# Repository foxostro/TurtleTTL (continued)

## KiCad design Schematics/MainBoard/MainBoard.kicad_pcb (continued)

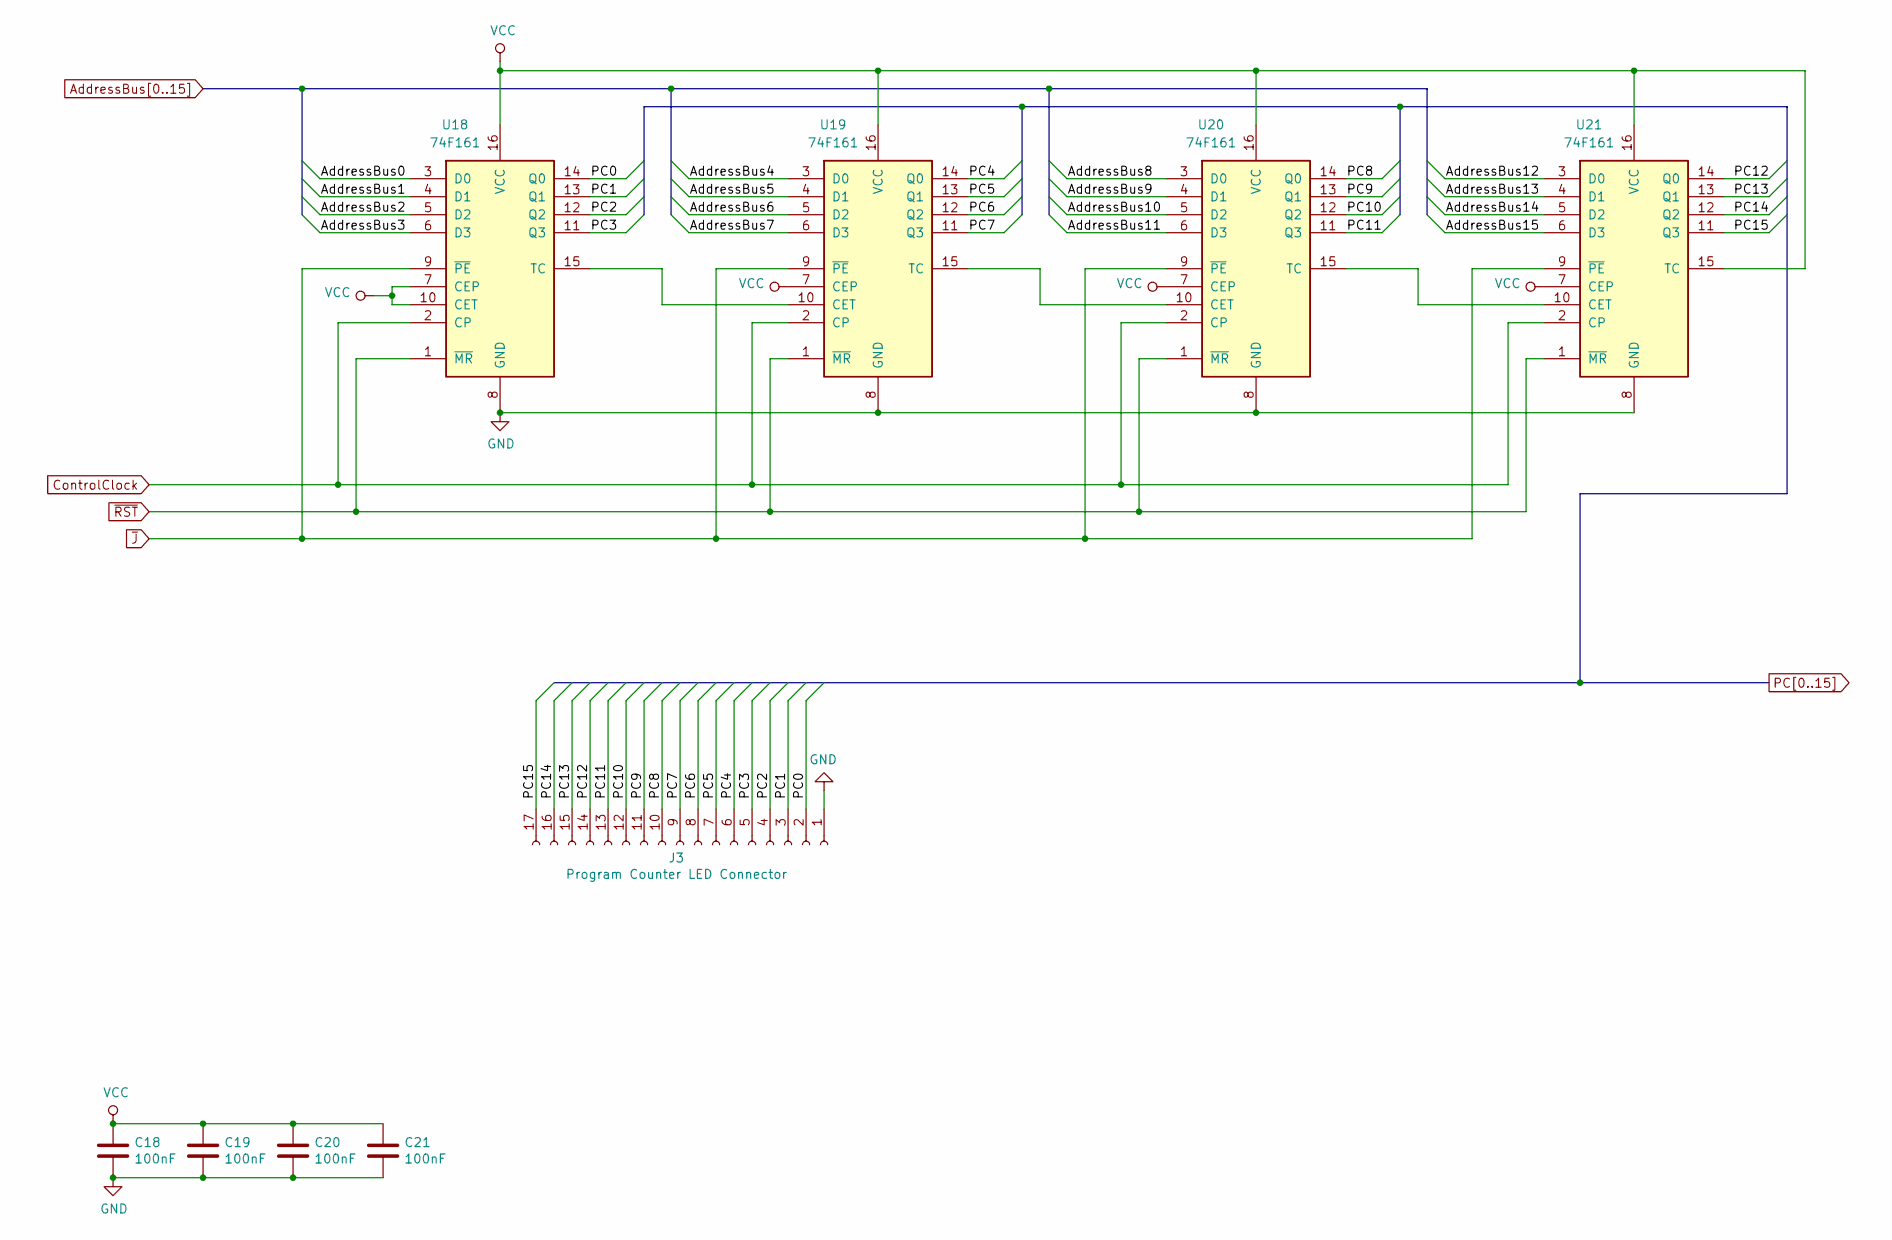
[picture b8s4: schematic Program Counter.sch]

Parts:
C18, C19, C20, C21: 100nF; C_Disc_D4.3mm_W1.9mm_P5.00mm
J3: Program Counter LED Connector; PinSocket_1x17_P2.54mm_Vertical
U18, U19, U20, U21: 74F161; DIP-16_W7.62mm

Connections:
AddressBus0: U18.3 (D0); also elsewhere on the board
AddressBus1: U18.4 (D1); also elsewhere on the board
AddressBus2: U18.5 (D2); also elsewhere on the board
AddressBus3: U18.6 (D3); also elsewhere on the board
AddressBus4: U19.3 (D0); also elsewhere on the board
AddressBus5: U19.4 (D1); also elsewhere on the board
AddressBus6: U19.5 (D2); also elsewhere on the board
AddressBus7: U19.6 (D3); also elsewhere on the board
AddressBus8: U20.3 (D0); also elsewhere on the board
AddressBus9: U20.4 (D1); also elsewhere on the board
AddressBus10: U20.5 (D2); also elsewhere on the board
AddressBus11: U20.6 (D3); also elsewhere on the board
AddressBus12: U21.3 (D0); also elsewhere on the board
AddressBus13: U21.4 (D1); also elsewhere on the board
AddressBus14: U21.5 (D2); also elsewhere on the board
AddressBus15: U21.6 (D3); also elsewhere on the board
ControlClock: U18.2 (CP), U19.2 (CP), U20.2 (CP), U21.2 (CP); also elsewhere on the board
GND: C18.2, C19.2, C20.2, C21.2, J3.1, U18.8 (GND), U19.8 (GND), U20.8 (GND), U21.8 (GND); also elsewhere on the board
unnamed: U18.15 (TC), U19.10 (CET)
unnamed: U19.15 (TC), U20.10 (CET)
unnamed: U20.15 (TC), U21.10 (CET)
PC0: J3.2, U18.14 (Q0); also elsewhere on the board
PC1: J3.3, U18.13 (Q1); also elsewhere on the board
PC2: J3.4, U18.12 (Q2); also elsewhere on the board
PC3: J3.5, U18.11 (Q3); also elsewhere on the board
PC4: J3.6, U19.14 (Q0); also elsewhere on the board
PC5: J3.7, U19.13 (Q1); also elsewhere on the board
PC6: J3.8, U19.12 (Q2); also elsewhere on the board
PC7: J3.9, U19.11 (Q3); also elsewhere on the board
PC8: J3.10, U20.14 (Q0); also elsewhere on the board
PC9: J3.11, U20.13 (Q1); also elsewhere on the board
PC10: J3.12, U20.12 (Q2); also elsewhere on the board
PC11: J3.13, U20.11 (Q3); also elsewhere on the board
PC12: J3.14, U21.14 (Q0); also elsewhere on the board
PC13: J3.15, U21.13 (Q1); also elsewhere on the board
PC14: J3.16, U21.12 (Q2); also elsewhere on the board
PC15: J3.17, U21.11 (Q3); also elsewhere on the board
VCC: C18.1, C19.1, C20.1, C21.1, U18.7 (CEP), U18.10 (CET), U18.16 (VCC), U19.7 (CEP), U19.16 (VCC), U20.7 (CEP), U20.16 (VCC), U21.7 (CEP), U21.15 (TC), U21.16 (VCC); also elsewhere on the board
~J: U18.9 (~PE), U19.9 (~PE), U20.9 (~PE), U21.9 (~PE); also elsewhere on the board
~RST: U18.1 (~MR), U19.1 (~MR), U20.1 (~MR), U21.1 (~MR); also elsewhere on the board

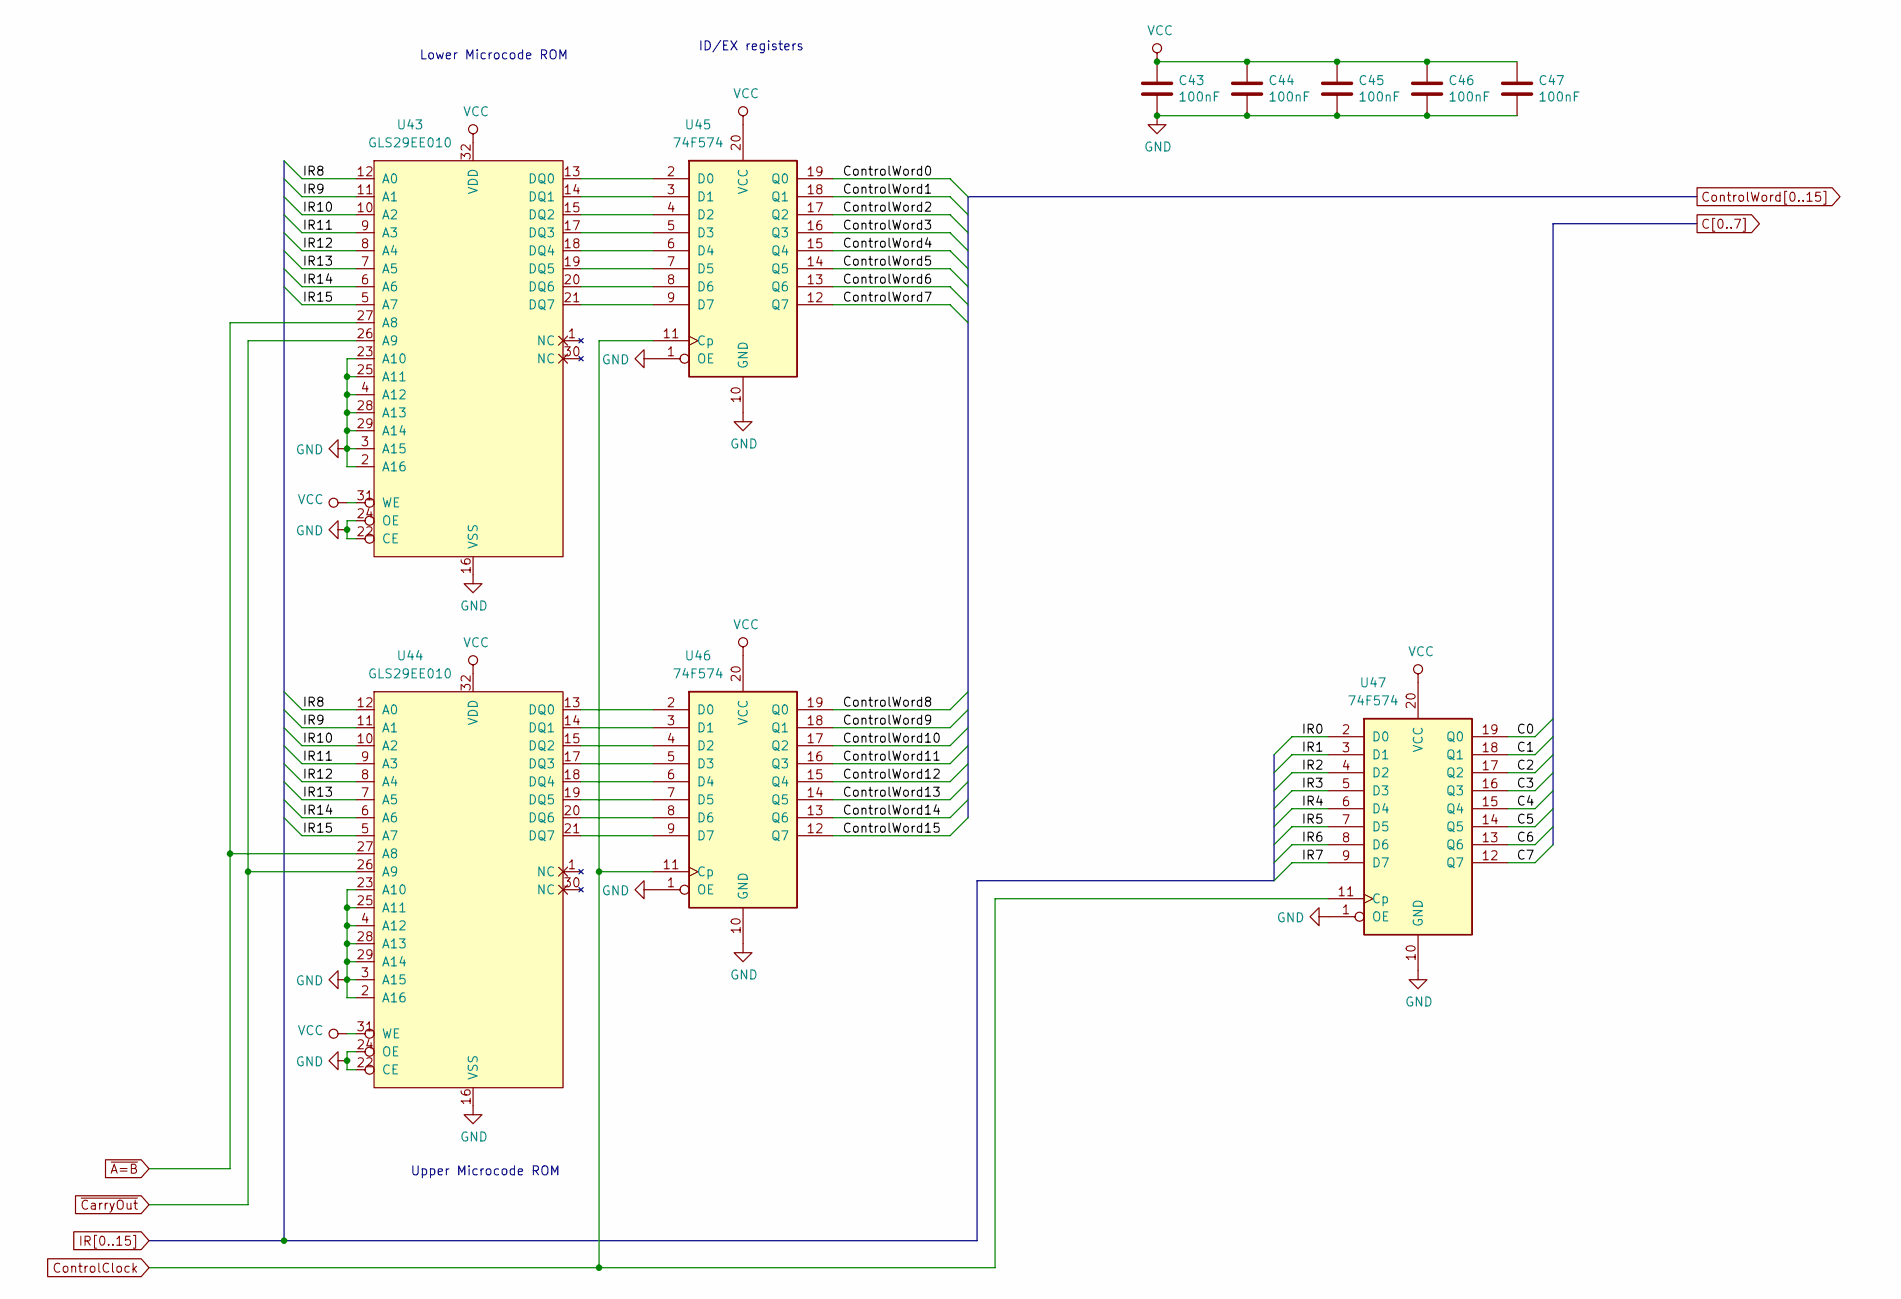
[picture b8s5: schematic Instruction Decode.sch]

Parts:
C43, C44, C45, C46, C47: 100nF; C_Disc_D4.3mm_W1.9mm_P5.00mm
U43, U44: GLS29EE010; DIP-32_W15.24mm_Socket
U45, U46, U47: 74F574; DIP-20_W7.62mm

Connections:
C0: U47.19 (Q0); also elsewhere on the board
C1: U47.18 (Q1); also elsewhere on the board
C2: U47.17 (Q2); also elsewhere on the board
C3: U47.16 (Q3); also elsewhere on the board
C4: U47.15 (Q4); also elsewhere on the board
C5: U47.14 (Q5); also elsewhere on the board
C6: U47.13 (Q6); also elsewhere on the board
C7: U47.12 (Q7); also elsewhere on the board
ControlClock: U45.11 (Cp), U46.11 (Cp), U47.11 (Cp); also elsewhere on the board
GND: C43.2, C44.2, C45.2, C46.2, C47.2, U43.2 (A16), U43.3 (A15), U43.4 (A12), U43.16 (VSS), U43.22 (CE), U43.23 (A10), U43.24 (OE), U43.25 (A11), U43.28 (A13), U43.29 (A14), U44.2 (A16), U44.3 (A15), U44.4 (A12), U44.16 (VSS), U44.22 (CE), U44.23 (A10), U44.24 (OE), U44.25 (A11), U44.28 (A13), U44.29 (A14), U45.1 (OE), U45.10 (GND), U46.1 (OE), U46.10 (GND), U47.1 (OE), U47.10 (GND); also elsewhere on the board
IR0: U47.2 (D0); also elsewhere on the board
IR1: U47.3 (D1); also elsewhere on the board
IR2: U47.4 (D2); also elsewhere on the board
IR3: U47.5 (D3); also elsewhere on the board
IR4: U47.6 (D4); also elsewhere on the board
IR5: U47.7 (D5); also elsewhere on the board
IR6: U47.8 (D6); also elsewhere on the board
IR7: U47.9 (D7); also elsewhere on the board
IR8: U43.12 (A0), U44.12 (A0); also elsewhere on the board
IR9: U43.11 (A1), U44.11 (A1); also elsewhere on the board
IR10: U43.10 (A2), U44.10 (A2); also elsewhere on the board
IR11: U43.9 (A3), U44.9 (A3); also elsewhere on the board
IR12: U43.8 (A4), U44.8 (A4); also elsewhere on the board
IR13: U43.7 (A5), U44.7 (A5); also elsewhere on the board
IR14: U43.6 (A6), U44.6 (A6); also elsewhere on the board
IR15: U43.5 (A7), U44.5 (A7); also elsewhere on the board
unnamed: U43.13 (DQ0), U45.2 (D0)
unnamed: U43.14 (DQ1), U45.3 (D1)
unnamed: U43.15 (DQ2), U45.4 (D2)
unnamed: U43.17 (DQ3), U45.5 (D3)
unnamed: U43.18 (DQ4), U45.6 (D4)
unnamed: U43.19 (DQ5), U45.7 (D5)
unnamed: U43.20 (DQ6), U45.8 (D6)
unnamed: U43.21 (DQ7), U45.9 (D7)
unnamed: U44.13 (DQ0), U46.2 (D0)
unnamed: U44.14 (DQ1), U46.3 (D1)
unnamed: U44.15 (DQ2), U46.4 (D2)
unnamed: U44.17 (DQ3), U46.5 (D3)
unnamed: U44.18 (DQ4), U46.6 (D4)
unnamed: U44.19 (DQ5), U46.7 (D5)
unnamed: U44.20 (DQ6), U46.8 (D6)
unnamed: U44.21 (DQ7), U46.9 (D7)
VCC: C43.1, C44.1, C45.1, C46.1, C47.1, U43.31 (WE), U43.32 (VDD), U44.31 (WE), U44.32 (VDD), U45.20 (VCC), U46.20 (VCC), U47.20 (VCC); also elsewhere on the board
~A=B: U43.27 (A8), U44.27 (A8); also elsewhere on the board
~AI: U46.16 (Q3); also elsewhere on the board
~AO: U46.17 (Q2); also elsewhere on the board
~BI: U46.14 (Q5); also elsewhere on the board
~BO: U46.15 (Q4); also elsewhere on the board
~CO: U45.19 (Q0); also elsewhere on the board
~CarryOut: U43.26 (A9), U44.26 (A9); also elsewhere on the board
~DI: U46.13 (Q6); also elsewhere on the board
~EO: U46.19 (Q0); also elsewhere on the board
~FI: U46.18 (Q1); also elsewhere on the board
~HLT: U46.12 (Q7); also elsewhere on the board
~J: U45.18 (Q1); also elsewhere on the board
~PI: U45.12 (Q7); also elsewhere on the board
~PO: U45.13 (Q6); also elsewhere on the board
~XI: U45.16 (Q3); also elsewhere on the board
~XO: U45.14 (Q5); also elsewhere on the board
~YI: U45.17 (Q2); also elsewhere on the board
~YO: U45.15 (Q4); also elsewhere on the board

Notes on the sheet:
ID/EX registers
Lower Microcode ROM
Upper Microcode ROM

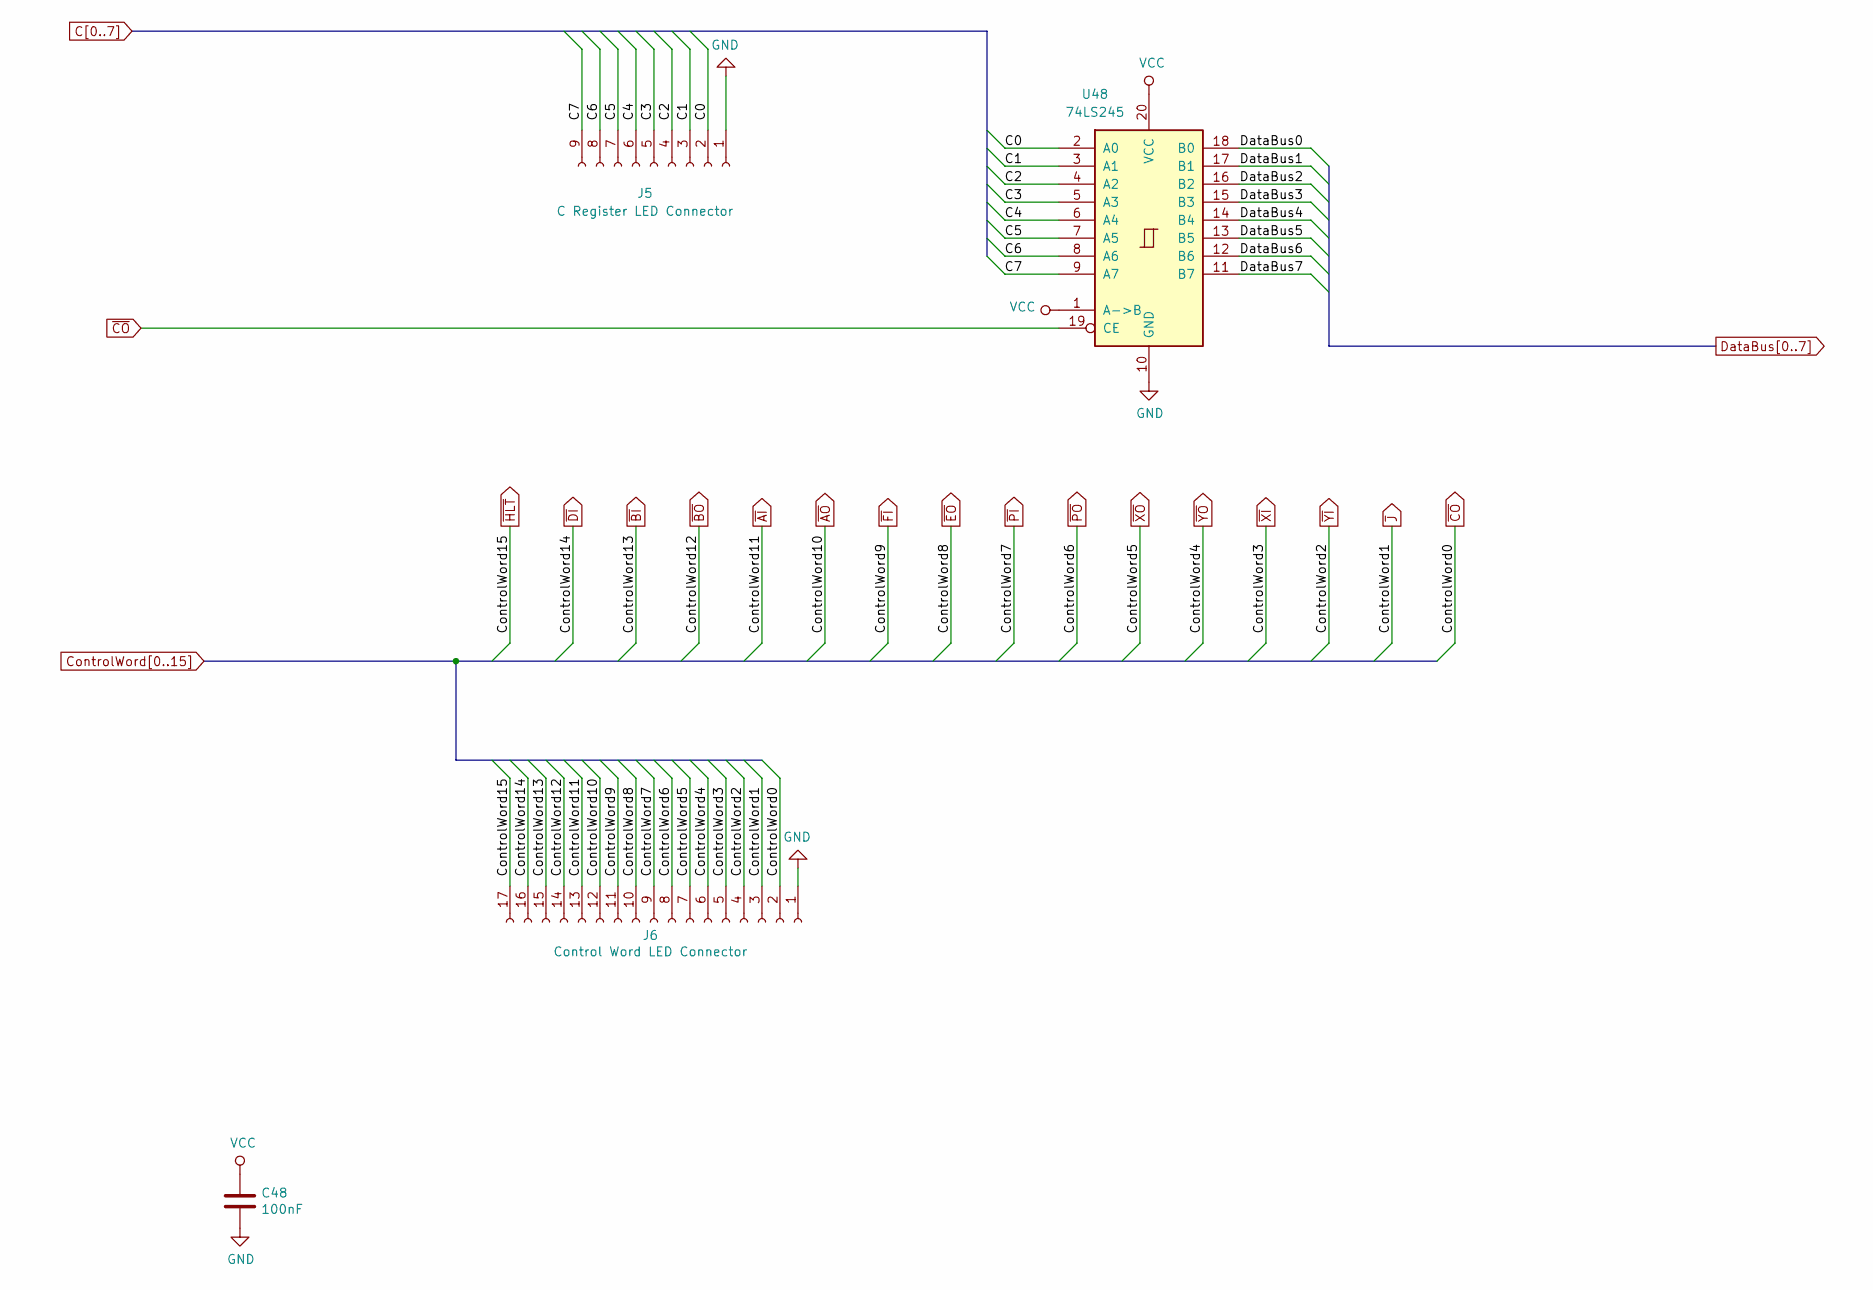
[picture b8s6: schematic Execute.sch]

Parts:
C48: 100nF; C_Disc_D4.3mm_W1.9mm_P5.00mm
J5: C Register LED Connector; PinSocket_1x09_P2.54mm_Vertical
J6: Control Word LED Connector; PinSocket_1x17_P2.54mm_Vertical
U48: 74LS245; DIP-20_W7.62mm_Socket

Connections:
C0: J5.2, U48.2 (A0); also elsewhere on the board
C1: J5.3, U48.3 (A1); also elsewhere on the board
C2: J5.4, U48.4 (A2); also elsewhere on the board
C3: J5.5, U48.5 (A3); also elsewhere on the board
C4: J5.6, U48.6 (A4); also elsewhere on the board
C5: J5.7, U48.7 (A5); also elsewhere on the board
C6: J5.8, U48.8 (A6); also elsewhere on the board
C7: J5.9, U48.9 (A7); also elsewhere on the board
DataBus0: U48.18 (B0); also elsewhere on the board
DataBus1: U48.17 (B1); also elsewhere on the board
DataBus2: U48.16 (B2); also elsewhere on the board
DataBus3: U48.15 (B3); also elsewhere on the board
DataBus4: U48.14 (B4); also elsewhere on the board
DataBus5: U48.13 (B5); also elsewhere on the board
DataBus6: U48.12 (B6); also elsewhere on the board
DataBus7: U48.11 (B7); also elsewhere on the board
GND: C48.2, J5.1, J6.1, U48.10 (GND); also elsewhere on the board
VCC: C48.1, U48.1 (A->B), U48.20 (VCC); also elsewhere on the board
~AI: J6.13; also elsewhere on the board
~AO: J6.12; also elsewhere on the board
~BI: J6.15; also elsewhere on the board
~BO: J6.14; also elsewhere on the board
~CO: J6.2, U48.19 (CE); also elsewhere on the board
~DI: J6.16; also elsewhere on the board
~EO: J6.10; also elsewhere on the board
~FI: J6.11; also elsewhere on the board
~HLT: J6.17; also elsewhere on the board
~J: J6.3; also elsewhere on the board
~PI: J6.9; also elsewhere on the board
~PO: J6.8; also elsewhere on the board
~XI: J6.5; also elsewhere on the board
~XO: J6.7; also elsewhere on the board
~YI: J6.4; also elsewhere on the board
~YO: J6.6; also elsewhere on the board

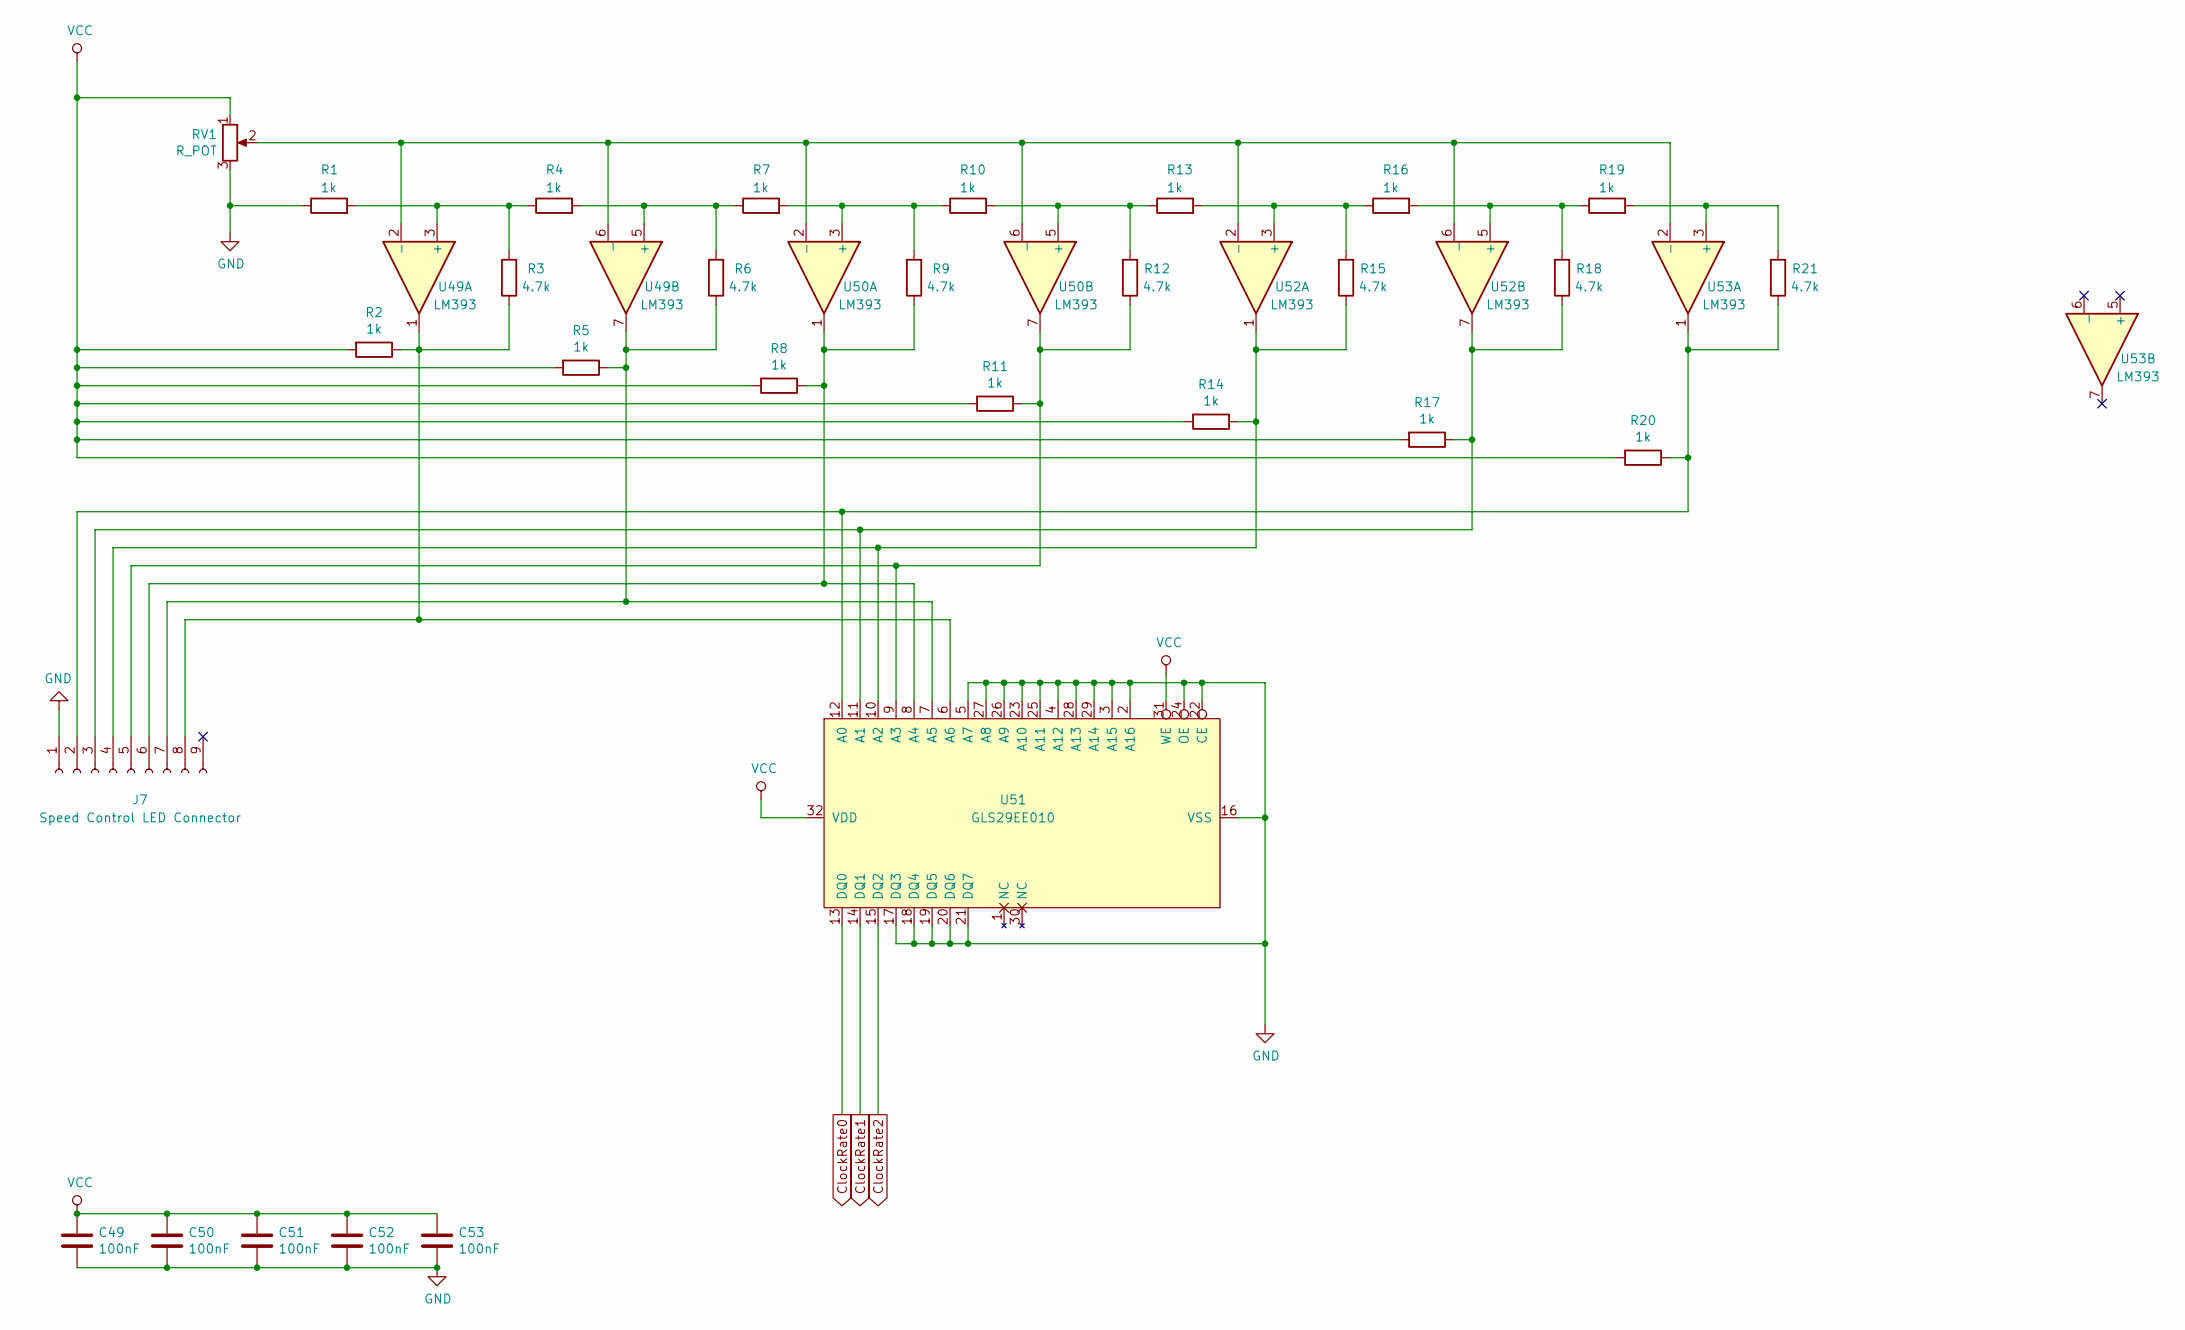
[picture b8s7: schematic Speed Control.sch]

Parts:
C49, C50, C51, C52, C53: 100nF; C_Disc_D4.3mm_W1.9mm_P5.00mm
J7: Speed Control LED Connector; PinSocket_1x09_P2.54mm_Vertical
R1, R2, R4, R5, R7, R8, R10, R11, R13, R14, R16, R17, R19, R20: 1k; R_Axial_DIN0207_L6.3mm_D2.5mm_P7.62mm_Horizontal
R3, R6, R9, R12, R15, R18, R21: 4.7k; R_Axial_DIN0207_L6.3mm_D2.5mm_P7.62mm_Horizontal
RV1: R_POT; Potentiometer_ACP_CA6-H2,5_Horizontal
U49, U50, U52, U53: LM393; DIP-8_W7.62mm
U51: GLS29EE010; DIP-32_W15.24mm_Socket

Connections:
ClockRate0: U51.13 (DQ0); also elsewhere on the board
ClockRate1: U51.14 (DQ1); also elsewhere on the board
ClockRate2: U51.15 (DQ2); also elsewhere on the board
GND: C49.2, C50.2, C51.2, C52.2, C53.2, J7.1, R1.1, RV1.3, U51.2 (A16), U51.3 (A15), U51.4 (A12), U51.5 (A7), U51.16 (VSS), U51.17 (DQ3), U51.18 (DQ4), U51.19 (DQ5), U51.20 (DQ6), U51.21 (DQ7), U51.22 (CE), U51.23 (A10), U51.24 (OE), U51.25 (A11), U51.26 (A9), U51.27 (A8), U51.28 (A13), U51.29 (A14); also elsewhere on the board
unnamed: J7.2, R20.1, R21.1, U51.12 (A0), U53.1
unnamed: J7.3, R17.1, R18.1, U51.11 (A1), U52.7
unnamed: J7.4, R14.1, R15.1, U51.10 (A2), U52.1
unnamed: J7.5, R11.1, R12.1, U50.7, U51.9 (A3)
unnamed: J7.6, R8.1, R9.1, U50.1, U51.8 (A4)
unnamed: J7.7, R5.1, R6.1, U49.7, U51.7 (A5)
unnamed: J7.8, R2.1, R3.1, U49.1, U51.6 (A6)
unnamed: R1.2, R3.2, R4.1, U49.3 (+)
unnamed: R4.2, R6.2, R7.1, U49.5 (+)
unnamed: R7.2, R9.2, R10.1, U50.3 (+)
unnamed: R10.2, R12.2, R13.1, U50.5 (+)
unnamed: R13.2, R15.2, R16.1, U52.3 (+)
unnamed: R16.2, R18.2, R19.1, U52.5 (+)
unnamed: R19.2, R21.2, U53.3 (+)
unnamed: RV1.2, U49.2 (-), U49.6 (_), U50.2 (-), U50.6 (_), U52.2 (-), U52.6 (_), U53.2 (-)
VCC: C49.1, C50.1, C51.1, C52.1, C53.1, R2.2, R5.2, R8.2, R11.2, R14.2, R17.2, R20.2, RV1.1, U51.31 (WE), U51.32 (VDD); also elsewhere on the board

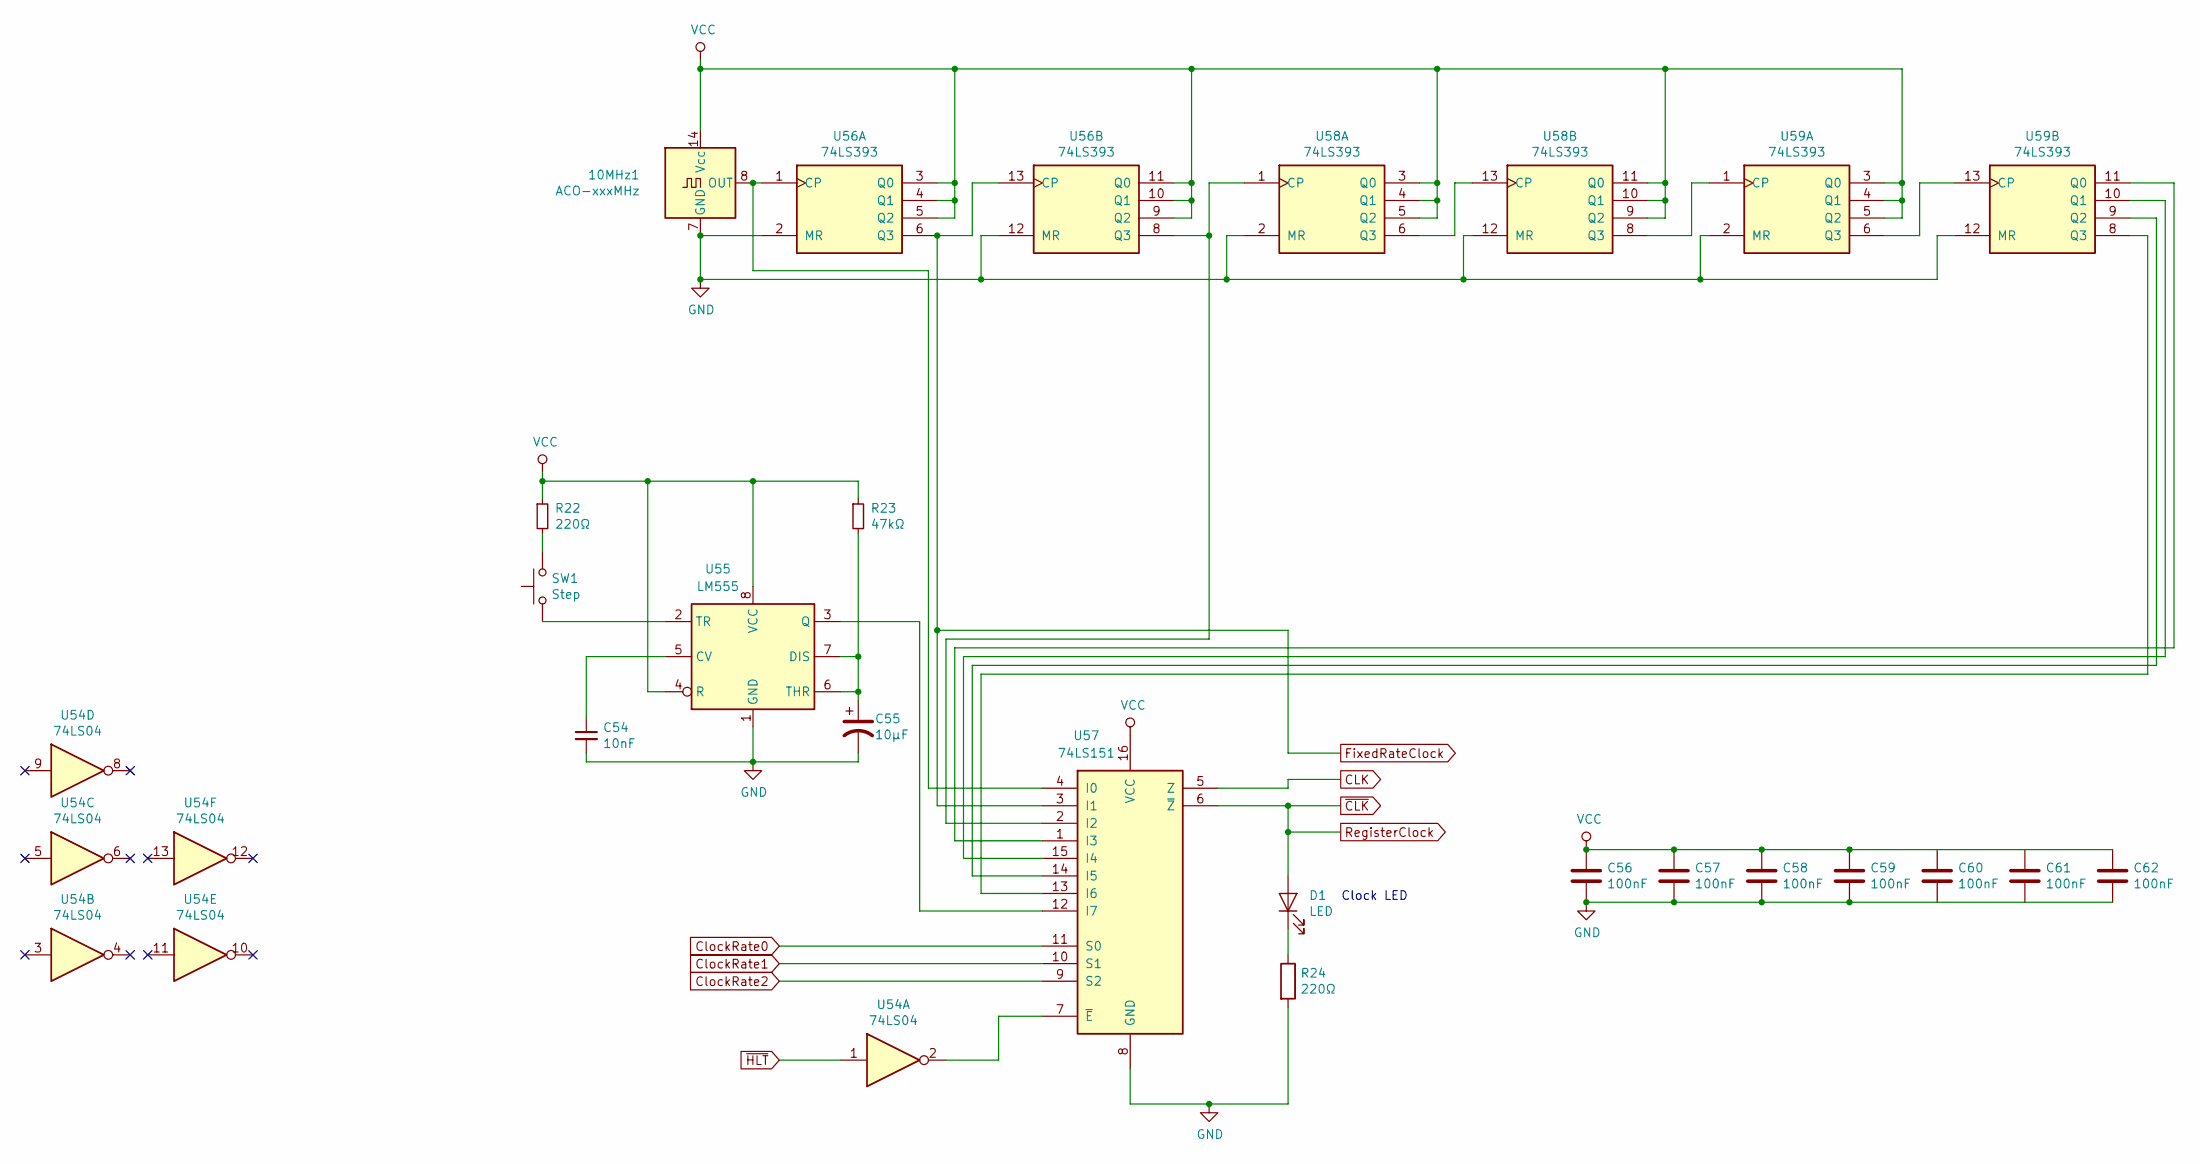
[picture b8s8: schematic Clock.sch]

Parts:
10MHz1: ACO-xxxMHz; Oscillator_DIP-14
C54: 10nF; C_Disc_D4.3mm_W1.9mm_P5.00mm
C55: 10µF; CP_Radial_D5.0mm_P2.00mm
C56, C57, C58, C59, C60, C61, C62: 100nF; C_Disc_D4.3mm_W1.9mm_P5.00mm
D1: LED; LED_D5.0mm
R22, R24: 220Ω; R_Axial_DIN0207_L6.3mm_D2.5mm_P7.62mm_Horizontal
R23: 47kΩ; R_Axial_DIN0207_L6.3mm_D2.5mm_P7.62mm_Horizontal
SW1: Step; SW_PUSH_6mm_H5mm
U54: 74LS04; DIP-14_W7.62mm
U55: LM555; DIP-8_W7.62mm
U56, U58, U59: 74LS393; DIP-14_W7.62mm
U57: 74LS151; DIP-16_W7.62mm

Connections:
CLK: U57.5 (Z); also elsewhere on the board
ClockRate0: U57.11 (S0); also elsewhere on the board
ClockRate1: U57.10 (S1); also elsewhere on the board
ClockRate2: U57.9 (S2); also elsewhere on the board
FixedRateClock: U56.6 (Q3), U56.13 (CP), U57.3 (I1); also elsewhere on the board
GND: 10MHz1.7 (GND), C54.2, C55.2, C56.2, C57.2, C58.2, C59.2, C60.2, C61.2, C62.2, R24.2, U55.1 (GND), U56.2 (MR), U56.12 (MR), U57.8 (GND), U58.2 (MR), U58.12 (MR), U59.2 (MR), U59.12 (MR); also elsewhere on the board
unnamed: C54.1, U55.5 (CV)
unnamed: C55.1, R23.2, U55.6 (THR), U55.7 (DIS)
unnamed: D1.1 (K), R24.1
unnamed 152: 10MHz1.8 (OUT), U56.1 (CP), U57.4 (I0); also elsewhere on the board
unnamed: R22.2, SW1.2
unnamed: SW1.1, U55.2 (TR)
unnamed: U54.2, U57.7 (~E)
unnamed: U55.3 (Q), U57.12 (I7)
unnamed: U56.8 (Q3), U57.2 (I2), U58.1 (CP)
unnamed: U57.1 (I3), U59.11 (Q0)
unnamed: U57.13 (I6), U59.8 (Q3)
unnamed: U57.14 (I5), U59.9 (Q2)
unnamed: U57.15 (I4), U59.10 (Q1)
unnamed: U58.8 (Q3), U59.1 (CP)
unnamed: U58.6 (Q3), U58.13 (CP)
unnamed: U59.6 (Q3), U59.13 (CP)
RegisterClock: D1.2 (A), U57.6 (~Z); also elsewhere on the board
VCC: 10MHz1.14 (Vcc), C56.1, C57.1, C58.1, C59.1, C60.1, C61.1, C62.1, R22.1, R23.1, U55.4 (R), U55.8 (VCC), U56.3 (Q0), U56.4 (Q1), U56.5 (Q2), U56.9 (Q2), U56.10 (Q1), U56.11 (Q0), U57.16 (VCC), U58.3 (Q0), U58.4 (Q1), U58.5 (Q2), U58.9 (Q2), U58.10 (Q1), U58.11 (Q0), U59.3 (Q0), U59.4 (Q1), U59.5 (Q2); also elsewhere on the board
~HLT: U54.1; also elsewhere on the board

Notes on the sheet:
Clock LED

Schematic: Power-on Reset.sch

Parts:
C63: 10nF; C_Disc_D4.3mm_W1.9mm_P5.00mm
C64, C65, C66, C67, C68: 100nF; C_Disc_D4.3mm_W1.9mm_P5.00mm
D2: LED; LED_D5.0mm
R25: 1kΩ; R_Axial_DIN0207_L6.3mm_D2.5mm_P7.62mm_Horizontal
R26: 1MΩ; R_Axial_DIN0207_L6.3mm_D2.5mm_P7.62mm_Horizontal
R27: 220Ω; R_Axial_DIN0207_L6.3mm_D2.5mm_P7.62mm_Horizontal
SW2: Reset; SW_PUSH_6mm_H5mm
U60: LM555; DIP-8_W7.62mm
U61: MCP100-450D; TO-92
U62: 74LS04; DIP-14_W7.62mm
U63: 74LS08; DIP-14_W7.62mm
U64: 74LS157; DIP-16_W7.62mm

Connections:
CLK: U64.3 (I1a); also elsewhere on the board
ControlClock: U64.4 (Za); also elsewhere on the board
FixedRateClock: U64.2 (I0a); also elsewhere on the board
GND: C63.2, C64.2, C65.2, C66.2, C67.2, C68.2, R27.2, U60.1 (GND), U61.3 (VSS), U64.5 (I0b), U64.6 (I1b), U64.7 (Zb), U64.8 (GND), U64.9 (Zc), U64.10 (I1c), U64.11 (I0c), U64.12 (Zd), U64.13 (I1d), U64.14 (I0d), U64.15 (E); also elsewhere on the board
unnamed: C63.1, U60.5 (CV)
unnamed: C64.1, R26.2, U60.6 (THR), U60.7 (DIS)
unnamed: D2.1 (K), R27.1
unnamed: D2.2 (A), U61.1 (~RST), U63.2
unnamed: R25.2, SW2.2
unnamed: SW2.1, U60.2 (TR)
unnamed: U60.3 (Q), U62.1
unnamed: U62.2, U63.1
VCC: C65.1, C66.1, C67.1, C68.1, R25.1, R26.1, U60.4 (R), U60.8 (VCC), U61.2 (VDD), U64.16 (VCC); also elsewhere on the board
~RST: U63.3, U64.1 (S); also elsewhere on the board

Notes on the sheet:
Power-Ok LED

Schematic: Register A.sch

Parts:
C70, C71: 100nF; C_Disc_D4.3mm_W1.9mm_P5.00mm
J8: A Register LED Connector; PinSocket_1x09_P2.54mm_Vertical
U65: 74F377; DIP-20_W7.62mm
U66: 74LS245; DIP-20_W7.62mm_Socket

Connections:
A0: J8.2, U65.2 (Q0), U66.2 (A0); also elsewhere on the board
A1: J8.3, U65.5 (Q1), U66.3 (A1); also elsewhere on the board
A2: J8.4, U65.6 (Q2), U66.4 (A2); also elsewhere on the board
A3: J8.5, U65.9 (Q3), U66.5 (A3); also elsewhere on the board
A4: J8.6, U65.12 (Q4), U66.6 (A4); also elsewhere on the board
A5: J8.7, U65.15 (Q5), U66.7 (A5); also elsewhere on the board
A6: J8.8, U65.16 (Q6), U66.8 (A6); also elsewhere on the board
A7: J8.9, U65.19 (Q7), U66.9 (A7); also elsewhere on the board
DataBus0: U65.3 (D0), U66.18 (B0); also elsewhere on the board
DataBus1: U65.4 (D1), U66.17 (B1); also elsewhere on the board
DataBus2: U65.7 (D2), U66.16 (B2); also elsewhere on the board
DataBus3: U65.8 (D3), U66.15 (B3); also elsewhere on the board
DataBus4: U65.13 (D4), U66.14 (B4); also elsewhere on the board
DataBus5: U65.14 (D5), U66.13 (B5); also elsewhere on the board
DataBus6: U65.17 (D6), U66.12 (B6); also elsewhere on the board
DataBus7: U65.18 (D7), U66.11 (B7); also elsewhere on the board
GND: C70.2, C71.2, J8.1, U65.10 (GND), U66.10 (GND); also elsewhere on the board
RegisterClock: U65.11 (CP); also elsewhere on the board
VCC: C70.1, C71.1, U65.20 (VCC), U66.1 (A->B), U66.20 (VCC); also elsewhere on the board
~AI: U65.1 (~E); also elsewhere on the board
~AO: U66.19 (CE); also elsewhere on the board

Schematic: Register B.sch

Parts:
C72, C73: 100nF; C_Disc_D4.3mm_W1.9mm_P5.00mm
J9: B Register LED Connector; PinSocket_1x09_P2.54mm_Vertical
U67: 74F377; DIP-20_W7.62mm
U68: 74LS245; DIP-20_W7.62mm_Socket

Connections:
B0: J9.2, U67.2 (Q0), U68.2 (A0); also elsewhere on the board
B1: J9.3, U67.5 (Q1), U68.3 (A1); also elsewhere on the board
B2: J9.4, U67.6 (Q2), U68.4 (A2); also elsewhere on the board
B3: J9.5, U67.9 (Q3), U68.5 (A3); also elsewhere on the board
B4: J9.6, U67.12 (Q4), U68.6 (A4); also elsewhere on the board
B5: J9.7, U67.15 (Q5), U68.7 (A5); also elsewhere on the board
B6: J9.8, U67.16 (Q6), U68.8 (A6); also elsewhere on the board
B7: J9.9, U67.19 (Q7), U68.9 (A7); also elsewhere on the board
DataBus0: U67.3 (D0), U68.18 (B0); also elsewhere on the board
DataBus1: U67.4 (D1), U68.17 (B1); also elsewhere on the board
DataBus2: U67.7 (D2), U68.16 (B2); also elsewhere on the board
DataBus3: U67.8 (D3), U68.15 (B3); also elsewhere on the board
DataBus4: U67.13 (D4), U68.14 (B4); also elsewhere on the board
DataBus5: U67.14 (D5), U68.13 (B5); also elsewhere on the board
DataBus6: U67.17 (D6), U68.12 (B6); also elsewhere on the board
DataBus7: U67.18 (D7), U68.11 (B7); also elsewhere on the board
GND: C72.2, C73.2, J9.1, U67.10 (GND), U68.10 (GND); also elsewhere on the board
RegisterClock: U67.11 (CP); also elsewhere on the board
VCC: C72.1, C73.1, U67.20 (VCC), U68.1 (A->B), U68.20 (VCC); also elsewhere on the board
~BI: U67.1 (~E); also elsewhere on the board
~BO: U68.19 (CE); also elsewhere on the board
